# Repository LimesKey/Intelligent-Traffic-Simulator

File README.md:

# Intelligent-Traffic-Simulator

> [!NOTE]
> Work in progress - Everything has shown to be working individually but has not came together as a whole yet

Detect how hot wheels cars navigate streets and interact with stop lights and how this can be applied to the real world. Just a thing I made for class

It detects hot wheels cars via the three coils embedded in the PCB traces. The coils are hooked up to a 555 timer at around 200 KHz and when the hot wheels car is over the coil, the frequency changes which is detected by the ESP32 running a pulse counter script. Essentially a metal/object detector specifically calibrated for hot wheels cars.

Potentiometers are just for debugging / testing out various configurations. There is a multiplexer hooked up to the ESP32 so that one microcontroller can control multiple LEDs for multiple traffic lights.

I made some small mistakes, but I believe I updated the schematic to reflect the changes I made to make it work.

### Todo: 
* better ESD/current backflow protection 
* have esp32 fully inside PCB outline rather than sticking out
* remove extra testpoints / optvbvvcional components now that I know what works
* look into using a general oscillator rather than a 555 timer for better performance/cost
* somehow make the usb-c connector much easier to solder, it's killing me how difficult it is
* integrate `object-detection.ino` with `dutch_traffic_light_code.ino`

# Media
## JLCPCB Ordered, Hand Assembled

## KiCad
### PCB 3D Viewer
<div style="display:flex; justify-content:center; gap:16px;">

</div>

### Schematic

<h4 align="center">Main controller</h4>

<h4 align="center">555 Timer Circuitry</h4>

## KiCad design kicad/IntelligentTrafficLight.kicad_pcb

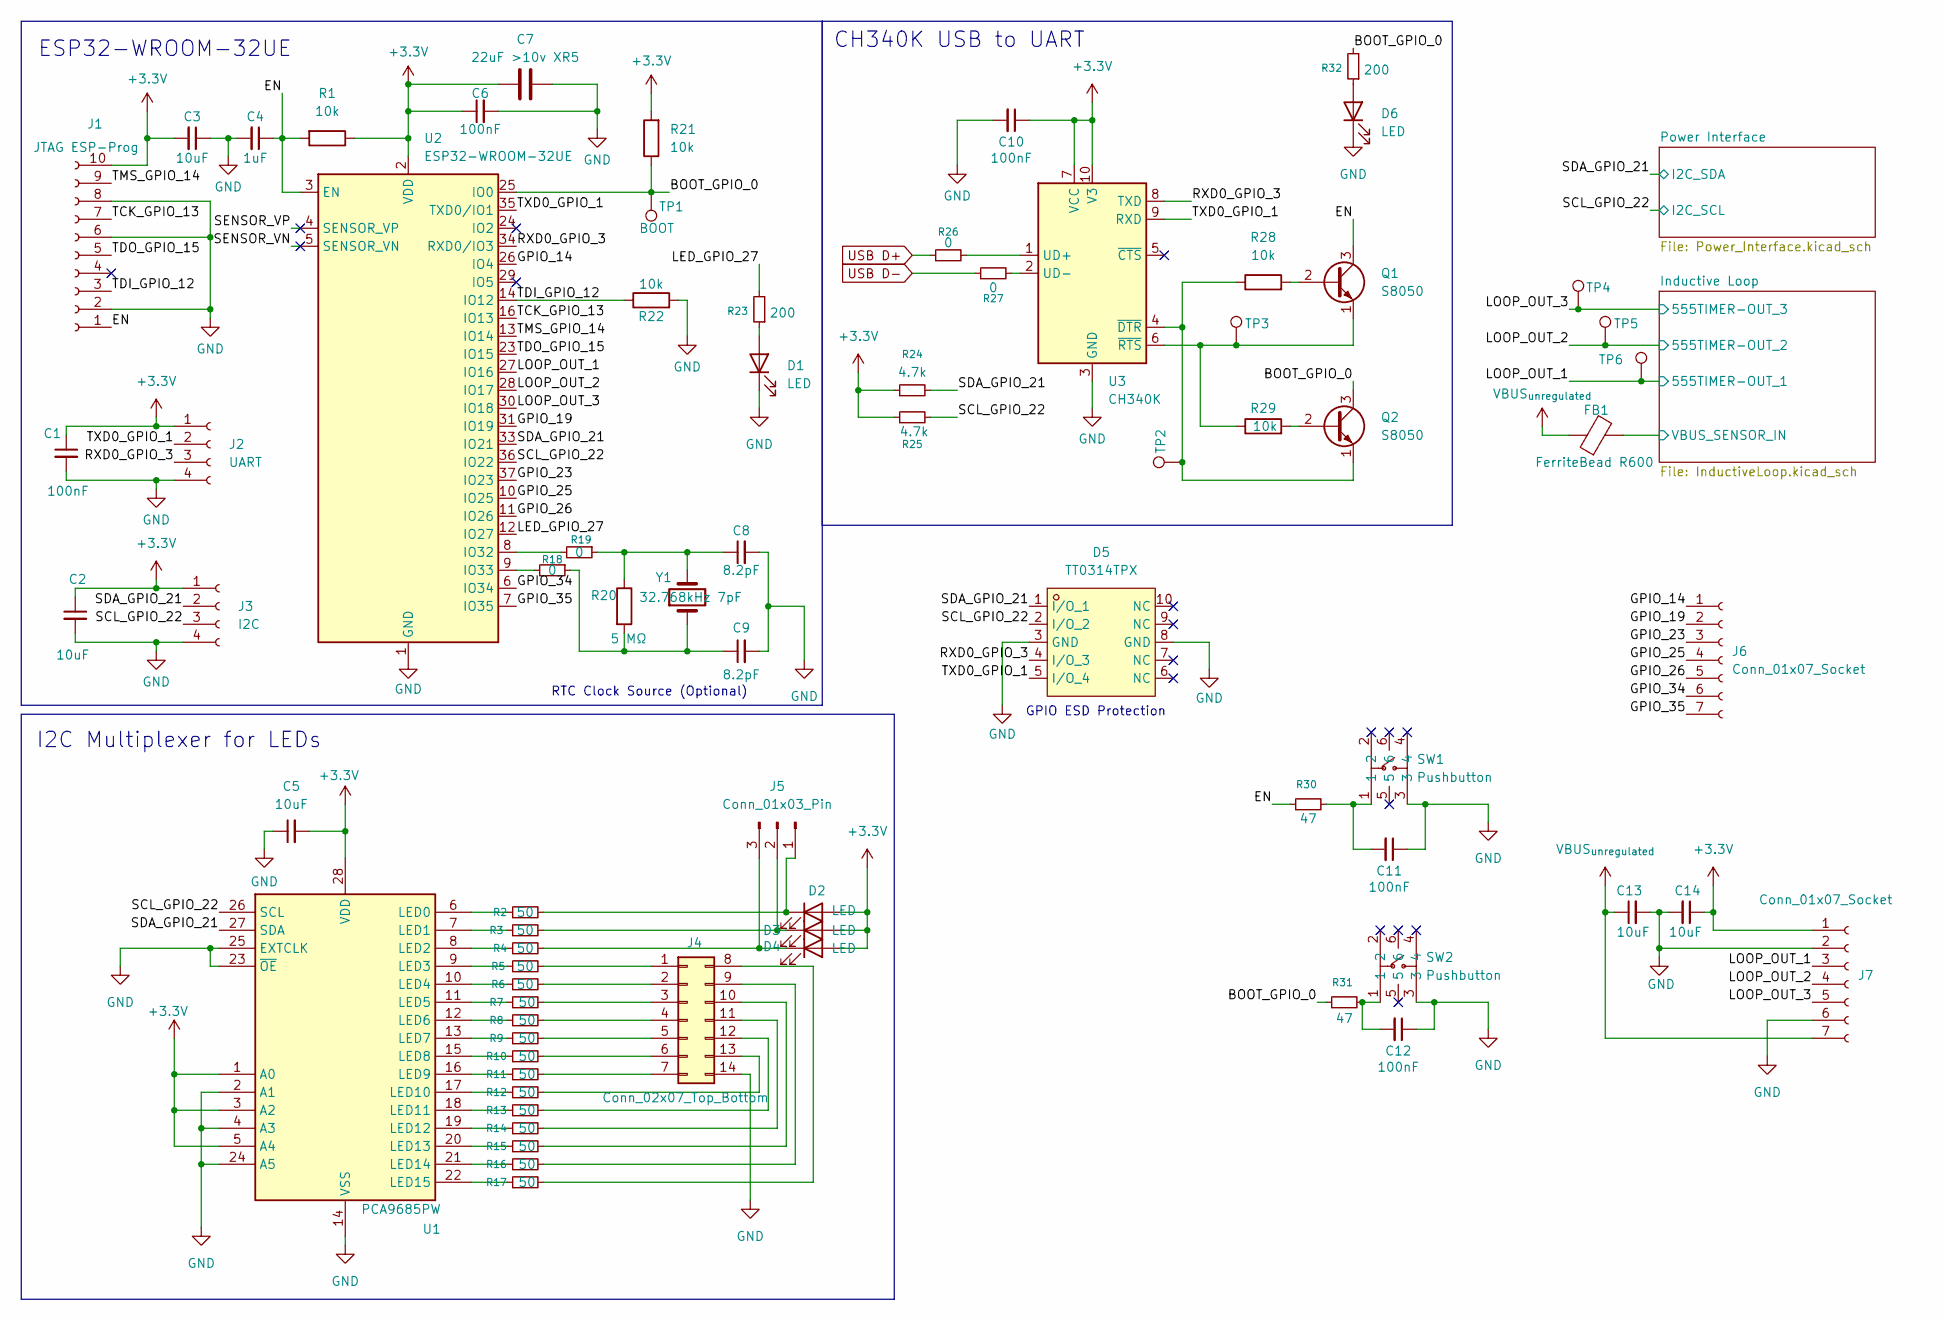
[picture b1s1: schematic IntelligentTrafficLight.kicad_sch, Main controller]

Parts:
C1, C6, C10, C11, C12: 100nF; C_0402_1005Metric
C2, C3, C5: 10uF; C_0402_1005Metric
C4: 1uF; C_0402_1005Metric
C7: 22uF >10v XR5; C_0805_2012Metric
C8, C9: 8.2pF; C_0402_1005Metric; LCSC Part C2857971
C13, C14: 10uF; C_0402_1005Metric; LCSC Part C33595851
D1, D2, D3, D4, D6: LED; LED_D5.0mm
D5: TT0314TPX; DFN2510-10_L2.5-W1.0-P0.50-BL; LCSC Part C5307962
FB1: FerriteBead R600; L_0603_1608Metric
J1: JTAG ESP-Prog; PinSocket_1x10_P2.54mm_Horizontal
J2: UART; PinSocket_1x04_P2.54mm_Horizontal
J3: I2C; PinSocket_1x04_P2.54mm_Horizontal
J4: Conn_02x07_Top_Bottom; PinSocket_2x07_P2.54mm_Horizontal
J5: Conn_01x03_Pin; PinHeader_1x03_P1.00mm_Vertical
J6, J7: Conn_01x07_Socket; PinSocket_1x07_P2.54mm_Horizontal
Q1, Q2: S8050; TO-92_Inline
R1, R21, R22, R28, R29: 10k; R_0402_1005Metric
R2, R3, R4, R5, R6, R7, R8, R9, R10, R11, R12, R13, R14, R15, R16, R17: 50; R_0402_1005Metric
R18, R19, R26, R27: 0; R_0603_1608Metric
R20: 5 MΩ; R_0402_1005Metric
R23, R32: 200; R_0402_1005Metric
R24, R25: 4.7k; R_0402_1005Metric
R30, R31: 47; R_0402_1005Metric
SW1, SW2: Pushbutton; SW-SMD_6P-L5.2-W5.2-P3.70-LS6.4; LCSC Part C2848968
TP1: BOOT; TestPoint_Bridge_Pitch2.54mm_Drill0.7mm
TP2: DTR; TestPoint_Bridge_Pitch2.54mm_Drill0.7mm
TP3: RTS; TestPoint_Bridge_Pitch2.54mm_Drill0.7mm
TP4: LOOP_OUT_3; TestPoint_Bridge_Pitch2.54mm_Drill0.7mm
TP5: LOOP_OUT_2; TestPoint_Bridge_Pitch2.54mm_Drill0.7mm
TP6: LOOP_OUT_1; TestPoint_Bridge_Pitch2.54mm_Drill0.7mm
U1: PCA9685PW; TSSOP-28_4.4x9.7mm_P0.65mm; LCSC Part C2678753
U2: ESP32-WROOM-32UE
U3: CH340K; SSOP-10-1EP_3.9x4.9mm_P1mm_EP2.1x3.3mm
Y1: 32.768kHz 7pF; Crystal_SMD_2012-2Pin_2.0x1.2mm_HandSoldering; LCSC Part C2905364

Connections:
+3.3V: C1.1, C2.1, C3.2, C5.2, C6.1, C7.1, C10.1, C14.1, D2.2 (A), D3.2 (A), D4.2 (A), J1.10, J2.1, J3.1, J7.1, R1.1, R21.2, R24.1, R25.1, U1.1 (A0), U1.3 (A2), U1.5 (A4), U1.28 (VDD), U2.2 (VDD), U3.7 (VCC), U3.10 (V3); also elsewhere on the board
/BOOT_GPIO_0: Q2.3 (C), R21.1, R31.1, R32.2, TP1.1 (1_1), U2.25 (IO0)
/EN: C4.1, J1.1, Q1.3 (C), R1.2, R30.1, U2.3 (EN)
/GPIO_14: J6.1, U2.26 (IO4)
/GPIO_19: J6.2, U2.31 (IO19)
/GPIO_23: J6.3, U2.37 (IO23)
/GPIO_25: J6.4, U2.10 (IO25)
/GPIO_26: J6.5, U2.11 (IO26)
/GPIO_34: J6.6, U2.6 (IO34)
/GPIO_35: J6.7, U2.7 (IO35)
/Inductive Loop/VBUS_SENSOR_IN: FB1.2; also elsewhere on the board
/LED_GPIO_27: R23.2, U2.12 (IO27)
/LOOP_OUT_1: J7.3, TP6.1 (1_1), U2.27 (IO16); also elsewhere on the board
/LOOP_OUT_2: J7.4, TP5.1 (1_1), U2.28 (IO17); also elsewhere on the board
/LOOP_OUT_3: J7.5, TP4.1 (1_1), U2.30 (IO18); also elsewhere on the board
/RXD0_GPIO_3: D5.4 (I/O_3), J2.3, U2.34 (RXD0/IO3), U3.8 (TXD)
/SCL_GPIO_22: D5.2 (I/O_2), J3.3, R25.2, U1.26 (SCL), U2.36 (IO22); also elsewhere on the board
/SDA_GPIO_21: D5.1 (I/O_1), J3.2, R24.2, U1.27 (SDA), U2.33 (IO21); also elsewhere on the board
/SENSOR_VN: U2.5 (SENSOR_VN)
/SENSOR_VP: U2.4 (SENSOR_VP)
/TCK_GPIO_13: J1.7, U2.16 (IO13)
/TDI_GPIO_12: J1.3, R22.1, U2.14 (IO12)
/TDO_GPIO_15: J1.5, U2.23 (IO15)
/TMS_GPIO_14: J1.9, U2.13 (IO14)
/TXD0_GPIO_1: D5.5 (I/O_4), J2.2, U2.35 (TXD0/IO1), U3.9 (RXD)
GND: C1.2, C2.2, C3.1, C4.2, C5.1, C6.2, C7.2, C8.2, C9.2, C10.2, C11.1, C12.1, C13.2, C14.2, D1.1 (K), D5.3 (GND), D5.8 (GND), D6.1 (K), J1.2, J1.6, J1.8, J2.4, J3.4, J4.14, J7.2, J7.6, R22.2, SW1.3, SW2.3, U1.2 (A1), U1.4 (A3), U1.14 (VSS), U1.23 (~OE), U1.24 (A5), U1.25 (EXTCLK), U2.1 (GND), U2.15 (GND), U2.38 (GND), U2.39 (GND), U3.3 (GND), U3.11 (GND); also elsewhere on the board
unnamed: C8.1, R19.1, R20.1, Y1.2
unnamed: C9.1, R18.1, R20.2, Y1.1
unnamed: C11.2, R30.2, SW1.1
unnamed: C12.2, R31.2, SW2.1
unnamed: D1.2 (A), R23.1
unnamed 35: D2.1 (K), J5.1, R2.2; also elsewhere on the board
unnamed: D3.1 (K), J5.2, R3.2
unnamed 37: D4.1 (K), J5.3, R4.2; also elsewhere on the board
unnamed: D6.2 (A), R32.1
unnamed 41: J4.1, R5.2; also elsewhere on the board
unnamed 42: J4.2, R6.2; also elsewhere on the board
unnamed: J4.3, R7.2
unnamed: J4.4, R8.2
unnamed: J4.5, R9.2
unnamed: J4.6, R10.2
unnamed: J4.7, R11.2
unnamed: J4.8, R17.2
unnamed: J4.9, R16.2
unnamed: J4.10, R15.2
unnamed: J4.11, R14.2
unnamed: J4.12, R13.2
unnamed: J4.13, R12.2
unnamed: Q1.2 (B), R28.2
unnamed: Q1.1 (E), R29.1, TP3.1 (1_1), U3.6 (~RTS)
unnamed: Q2.2 (B), R29.2
unnamed: Q2.1 (E), R28.1, TP2.1 (1_1), U3.4 (~DTR)
unnamed 75: R2.1, U1.6 (LED0); also elsewhere on the board
unnamed: R3.1, U1.7 (LED1)
unnamed 77: R4.1, U1.8 (LED2); also elsewhere on the board
unnamed 78: R5.1, U1.9 (LED3); also elsewhere on the board
unnamed 79: R6.1, U1.10 (LED4); also elsewhere on the board
unnamed: R7.1, U1.11 (LED5)
unnamed: R8.1, U1.12 (LED6)
unnamed: R9.1, U1.13 (LED7)
unnamed: R10.1, U1.15 (LED8)
unnamed: R11.1, U1.16 (LED9)
unnamed: R12.1, U1.17 (LED10)
unnamed: R13.1, U1.18 (LED11)
unnamed: R14.1, U1.19 (LED12)
unnamed: R15.1, U1.20 (LED13)
unnamed: R16.1, U1.21 (LED14)
unnamed: R17.1, U1.22 (LED15)
unnamed: R19.2, U2.8 (IO32)
unnamed: R18.2, U2.9 (IO33)
unnamed: R26.2, U3.1 (UD+)
unnamed: R27.2, U3.2 (UD-)
USB D+: R26.1; also elsewhere on the board
USB D-: R27.1; also elsewhere on the board
VBUS_{unregulated}: C13.1, FB1.1, J7.7; also elsewhere on the board

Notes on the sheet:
RTC Clock Source (Optional)
ESP32-WROOM-32UE
GPIO ESD Protection
I2C Multiplexer for LEDs
CH340K USB to UART

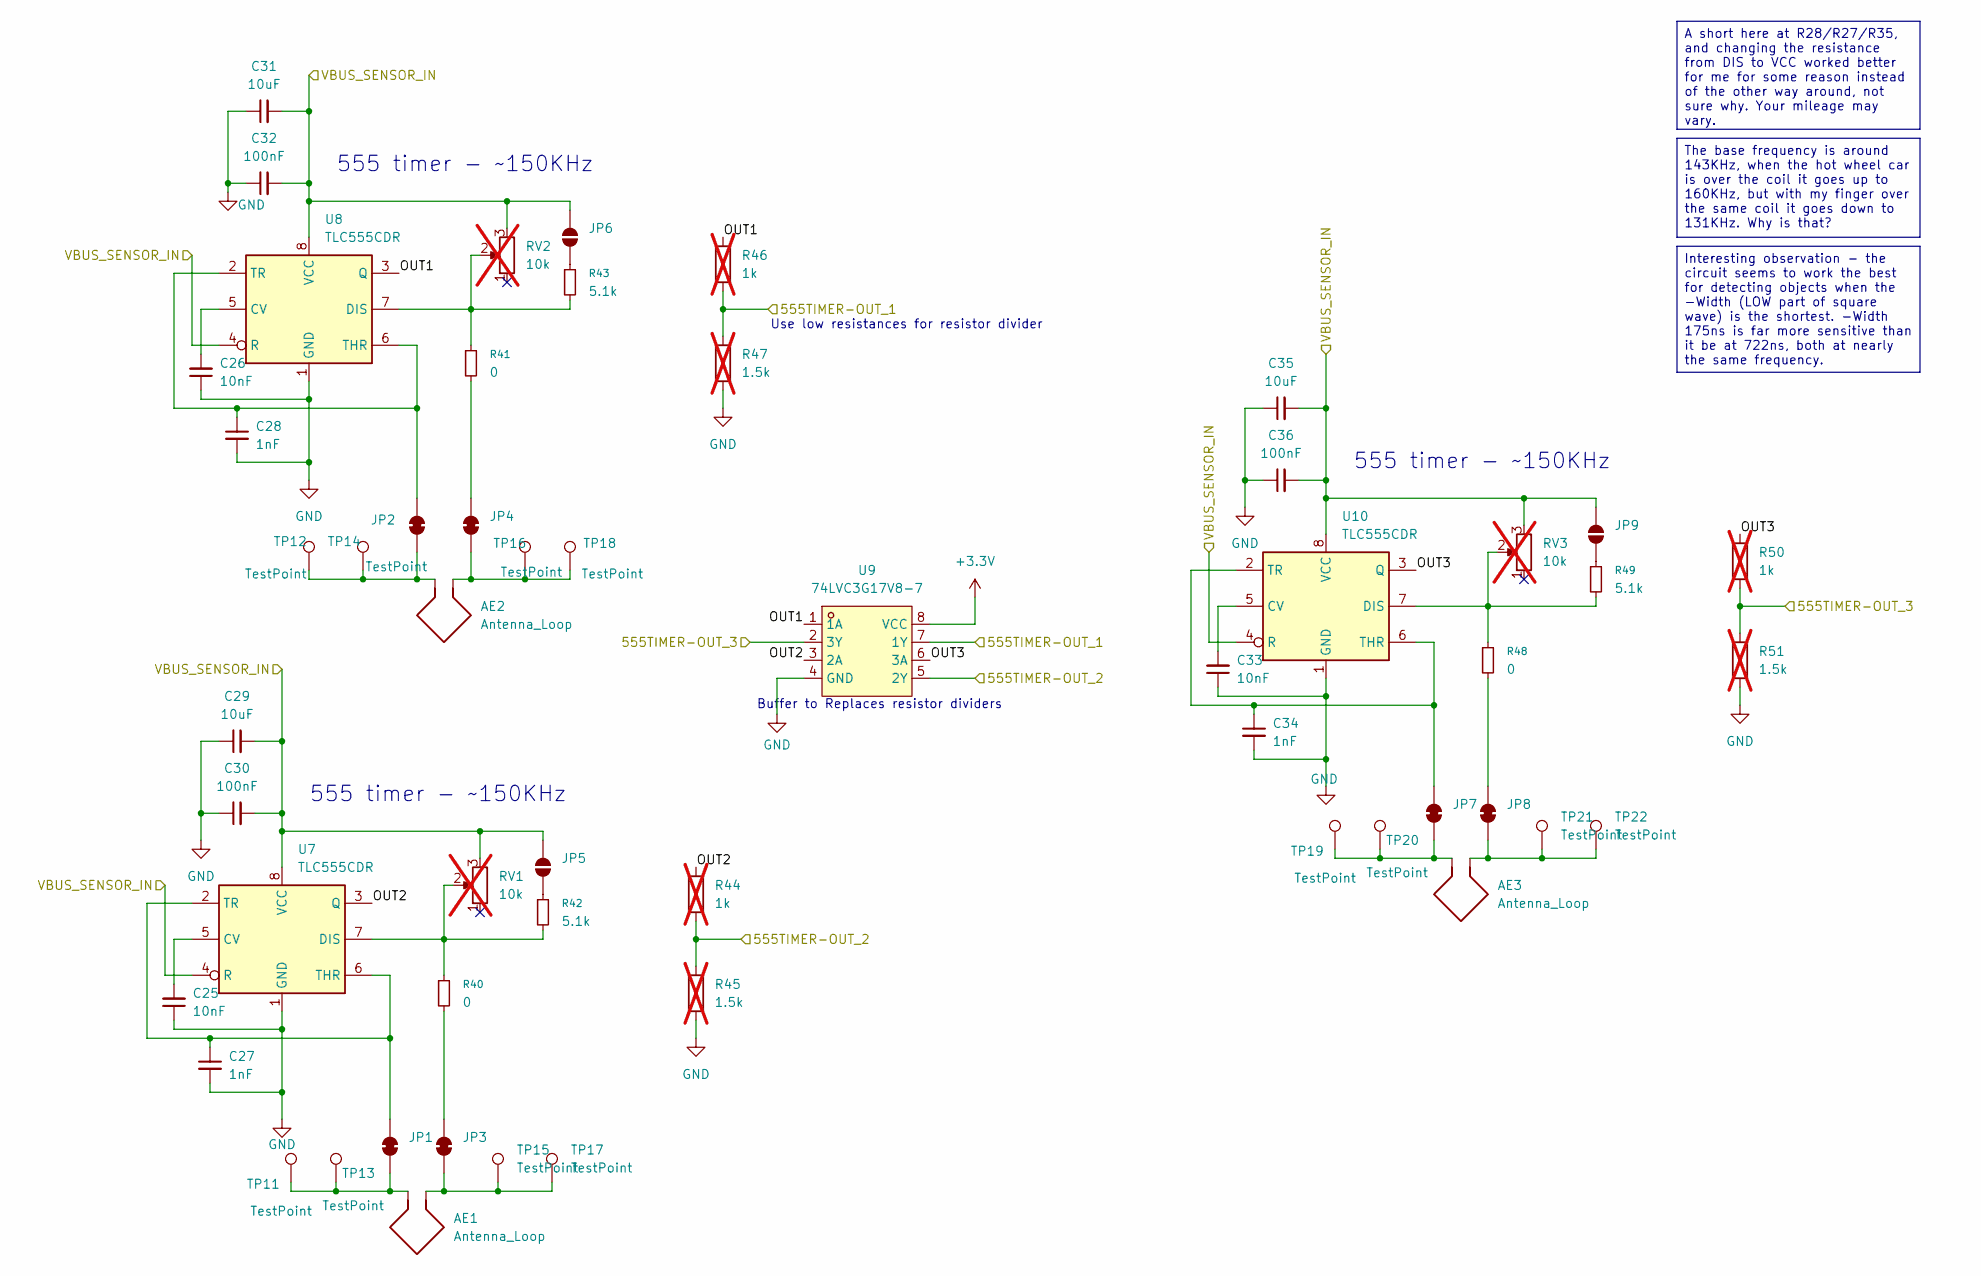
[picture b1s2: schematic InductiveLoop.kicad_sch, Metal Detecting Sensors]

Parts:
AE1, AE2, AE3: Antenna_Loop; HOTWHEEL_DETECTOR
C25, C26, C33: 10nF; C_0402_1005Metric
C27, C28, C34: 1nF; C_0402_1005Metric
C29, C31, C35: 10uF; C_0402_1005Metric
C30, C32, C36: 100nF; C_0402_1005Metric
JP1, JP2, JP3, JP4, JP7, JP8: SolderJumper_2_Bridged; SolderJumper-2_P1.3mm_Bridged_RoundedPad1.0x1.5mm
JP5, JP6, JP9: SolderJumper_2_Open; SolderJumper-2_P1.3mm_Open_RoundedPad1.0x1.5mm
R40, R41, R48: 0; R_0402_1005Metric
R42, R49: 5.1k; R_0402_1005Metric
R43: 5.1k; R_Axial_DIN0207_L6.3mm_D2.5mm_P10.16mm_Horizontal
R44, R46, R50: 1k; R_0402_1005Metric; not fitted
R45, R47, R51: 1.5k; R_0402_1005Metric; not fitted
RV1, RV2, RV3: 10k; Potentiometer_Bourns_3386P_Vertical; LCSC Part C118956; not fitted
TP11, TP12, TP13, TP14, TP15, TP16, TP17, TP18, TP19, TP20, TP21, TP22: TestPoint; PinSocket_1x01_P2.54mm_Vertical
U7, U8, U10: TLC555CDR; SOIC-8_3.9x4.9mm_P1.27mm; LCSC Part C6986
U9: 74LVC3G17V8-7; VSSOP-8_L2.1-W2.4-P0.50-LS3.2-BL; MPN 74LVC3G17V8-7; LCSC Part C19948350

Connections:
+3.3V: U9.8 (VCC); also elsewhere on the board
/Inductive Loop/OUT1: R46.1, U8.3 (Q), U9.1 (1A)
/Inductive Loop/OUT2: R44.1, U7.3 (Q), U9.3 (2A)
/Inductive Loop/OUT3: R50.1, U9.6 (3A), U10.3 (Q)
/Inductive Loop/VBUS_SENSOR_IN: C29.2, C30.2, C31.2, C32.2, C35.2, C36.2, JP5.2 (B), JP6.2 (B), JP9.2 (B), RV1.3, RV2.3, RV3.3, U7.4 (R), U7.8 (VCC), U8.4 (R), U8.8 (VCC), U10.4 (R), U10.8 (VCC); also elsewhere on the board
/LOOP_OUT_1: R46.2, R47.1, U9.7 (1Y); also elsewhere on the board
/LOOP_OUT_2: R44.2, R45.1, U9.5 (2Y); also elsewhere on the board
/LOOP_OUT_3: R50.2, R51.1, U9.2 (3Y); also elsewhere on the board
GND: C25.1, C26.1, C27.2, C28.2, C29.1, C30.1, C31.1, C32.1, C33.1, C34.2, C35.1, C36.1, R45.2, R47.2, R51.2, U7.1 (GND), U8.1 (GND), U9.4 (GND), U10.1 (GND); also elsewhere on the board
unnamed: AE1.2, JP1.1 (A), TP11.1 (1_1), TP13.1 (1_1)
unnamed: C27.1, JP1.2 (B), U7.2 (TR), U7.6 (THR)
unnamed: AE2.2, JP2.1 (A), TP12.1 (1_1), TP14.1 (1_1)
unnamed: C28.1, JP2.2 (B), U8.2 (TR), U8.6 (THR)
unnamed: AE1.1, JP3.1 (A), TP15.1 (1_1), TP17.1 (1_1)
unnamed: JP3.2 (B), R40.2
unnamed: AE2.1, JP4.1 (A), TP16.1 (1_1), TP18.1 (1_1)
unnamed: JP4.2 (B), R41.2
unnamed: JP5.1 (A), R42.1
unnamed: JP6.1 (A), R43.1
unnamed: AE3.2, JP7.1 (A), TP19.1 (1_1), TP20.1 (1_1)
unnamed: C34.1, JP7.2 (B), U10.2 (TR), U10.6 (THR)
unnamed: AE3.1, JP8.1 (A), TP21.1 (1_1), TP22.1 (1_1)
unnamed: JP8.2 (B), R48.2
unnamed: JP9.1 (A), R49.1
unnamed: C25.2, U7.5 (CV)
unnamed: R40.1, R42.2, RV1.2, U7.7 (DIS)
unnamed: C26.2, U8.5 (CV)
unnamed: R41.1, R43.2, RV2.2, U8.7 (DIS)
unnamed: C33.2, U10.5 (CV)
unnamed: R48.1, R49.2, RV3.2, U10.7 (DIS)

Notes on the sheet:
Buffer to Replaces resistor dividers
555 timer - ~150KHz
Use low resistances for resistor divider
Interesting observation - the circuit seems to work the best for detecting objects when the -Width (LOW part of square wave) is the shortest. -Width 175ns is far more sensitive than it be at 722ns, both at nearly the same frequency.
The base frequency is around 143KHz, when the hot wheel car is over the coil it goes up to 160KHz, but with my finger over the same coil it goes down to 131KHz. Why is that?
A short here at R28/R27/R35, and changing the resistance from DIS to VCC worked better for me for some reason instead of the other way around, not sure why. Your mileage may vary.

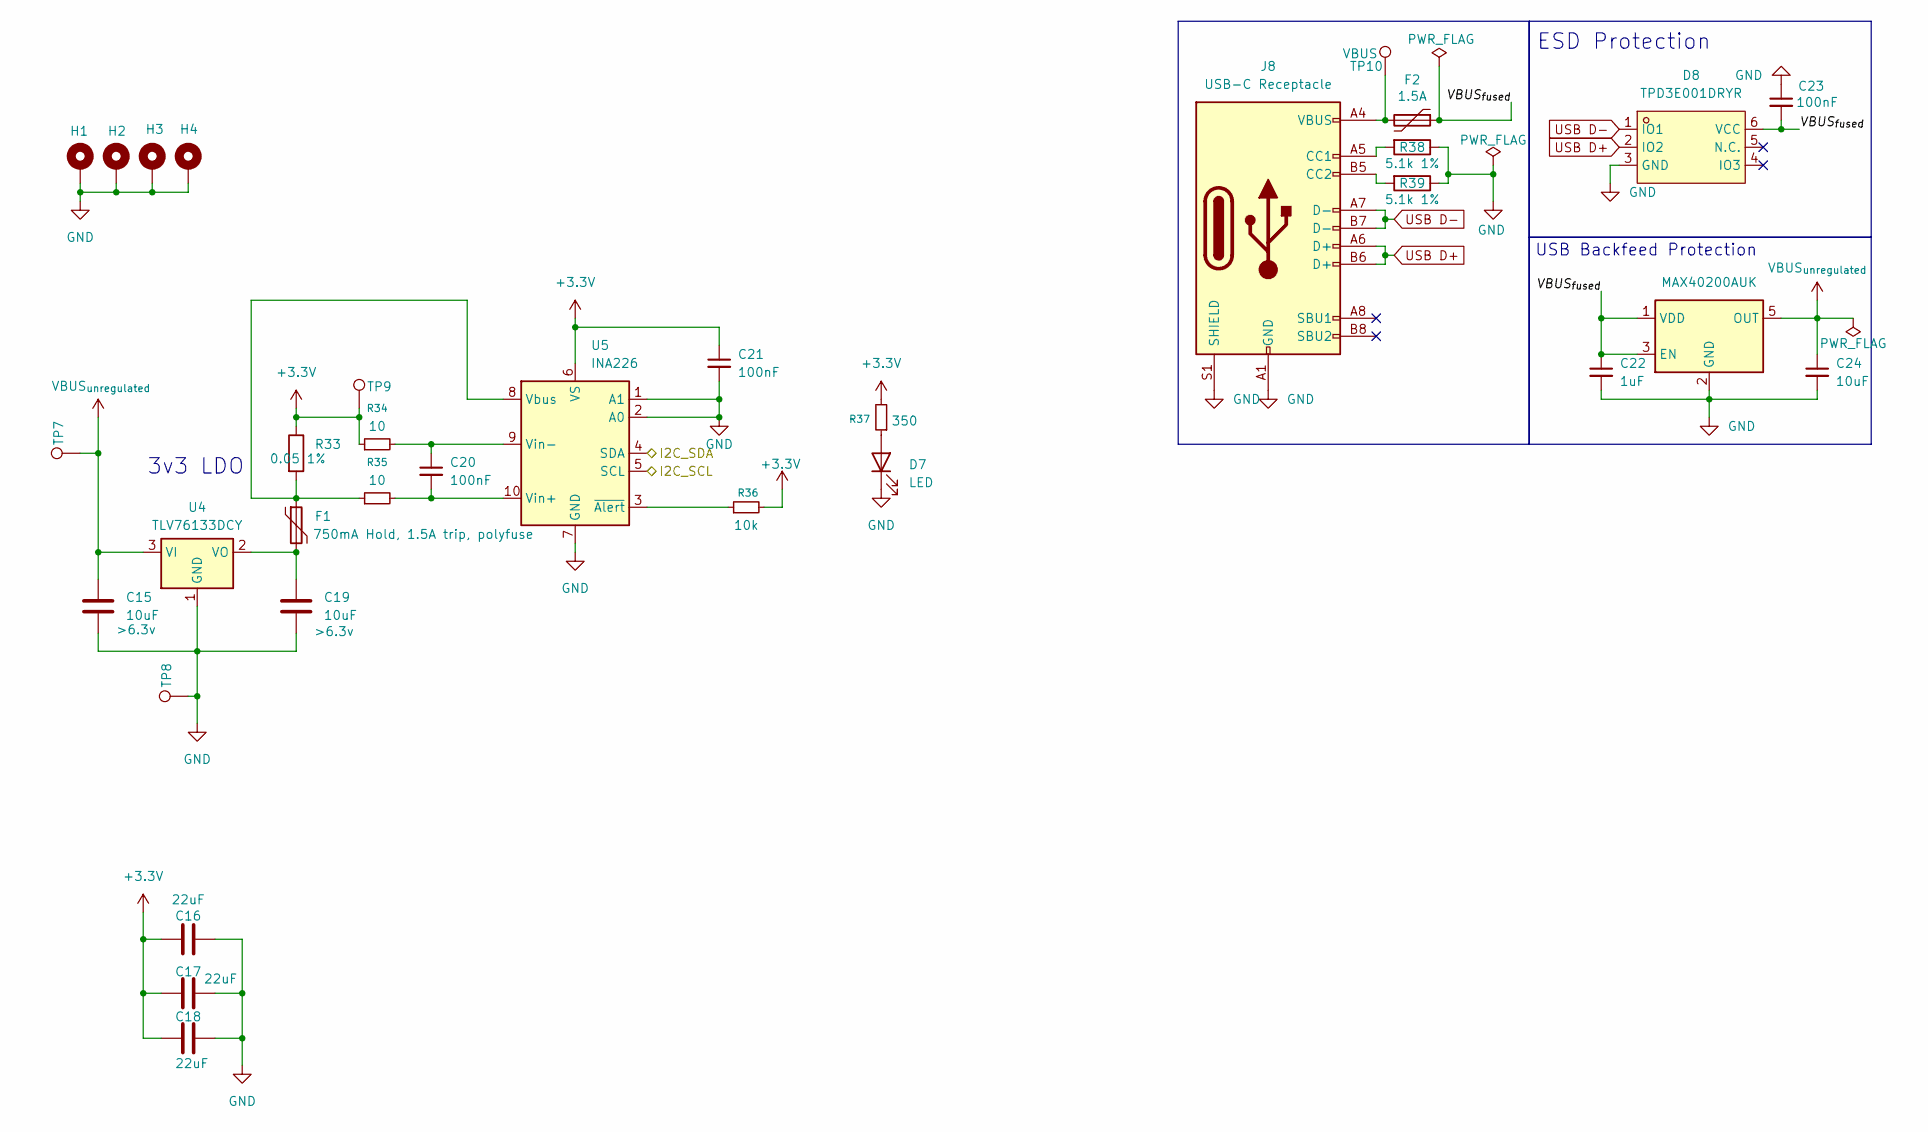
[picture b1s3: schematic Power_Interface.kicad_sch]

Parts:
C15, C19: 10uF; C_0402_1005Metric; Voltage Rating >6.3v
C16, C17, C18: 22uF; C_0805_2012Metric; LCSC Part C7472967
C20, C21: 100nF; C_0402_1005Metric
C22: 1uF; C_0402_1005Metric
C23: 100nF; C_0402_1005Metric; LCSC Part C392963
C24: 10uF; C_0402_1005Metric
D7: LED; LED_D5.0mm
D8: TPD3E001DRYR; Texas_USON-6_1x1.45mm_P0.5mm_SMD; LCSC Part C5122047
F1: 750mA Hold, 1.5A trip, polyfuse; Fuse_1812_4532Metric; LCSC Part C49318440
F2: 1.5A; Fuse_1206_3216Metric_Pad1.42x1.75mm_HandSolder; LCSC Part C883133
H1, H2, H3, H4: MountingHole_Pad; MountingHole_3.2mm_M3_Pad
J8: USB-C Receptacle; USB_C_Receptacle_G-Switch_GT-USB-7010ASV; LCSC Part C963413
R33: 0.05 1%; R_2512_6332Metric; LCSC Part C49164908
R34, R35: 10; R_0402_1005Metric
R36: 10k; R_0402_1005Metric
R37: 350; R_0402_1005Metric
R38, R39: 5.1k 1%; R_0402_1005Metric; LCSC Part C2906874
TP7: VBUSunreg; TestPoint_Bridge_Pitch2.54mm_Drill0.7mm
TP8: LOOP_OUT_2; TestPoint_Bridge_Pitch2.54mm_Drill0.7mm
TP9: 3V3; TestPoint_Bridge_Pitch2.54mm_Drill0.7mm
TP10: VBUS; PinSocket_1x01_P2.54mm_Vertical
U4: TLV76133DCY; SOT-223-3_TabPin2; LCSC Part C7527500
U5: INA226; TSSOP-10_3x3mm_P0.5mm
U6: MAX40200AUK; SOT-23-5

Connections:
+3.3V: C16.1, C17.1, C18.1, C21.1, R33.1, R34.1, R36.2, R37.2, TP9.1 (1_1), U5.6 (VS); also elsewhere on the board
/Power Interface/VBUS_{fused}: C22.1, C23.2, D8.6 (VCC), F2.1, U6.1 (VDD), U6.3 (EN)
/SCL_GPIO_22: U5.5 (SCL); also elsewhere on the board
/SDA_GPIO_21: U5.4 (SDA); also elsewhere on the board
GND: C15.2, C16.2, C17.2, C18.2, C19.2, C21.2, C22.2, C23.1, C24.2, D7.1 (K), D8.3 (GND), H1.1 (1_1), H2.1 (1_1), H3.1 (1_1), H4.1 (1_1), J8.A1 (GND), J8.A12 (GND), J8.B1 (GND), J8.B12 (GND), J8.S1 (SHIELD), R38.1, R39.1, TP8.1 (1_1), U4.1 (GND), U5.1 (A1), U5.2 (A0), U5.7 (GND), U6.2 (GND); also elsewhere on the board
unnamed: D7.2 (A), R37.1
unnamed: F2.2, J8.A4 (VBUS), J8.A9 (VBUS), J8.B4 (VBUS), J8.B9 (VBUS), TP10.1 (1_1)
unnamed: J8.A5 (CC1), R38.2
unnamed: J8.B5 (CC2), R39.2
unnamed: C19.1, F1.2, U4.2 (VO)
unnamed: F1.1, R33.2, R35.1, U5.8 (Vbus)
unnamed: C20.2, R35.2, U5.10 (Vin+)
unnamed: C20.1, R34.2, U5.9 (Vin-)
unnamed: R36.1, U5.3 (~Alert)
USB D+: D8.2 (IO2), J8.A6 (D+), J8.B6 (D+); also elsewhere on the board
USB D-: D8.1 (IO1), J8.A7 (D-), J8.B7 (D-); also elsewhere on the board
VBUS_{unregulated}: C15.1, C24.1, TP7.1 (1_1), U4.3 (VI), U6.5 (OUT); also elsewhere on the board

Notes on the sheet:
3v3 LDO
USB Backfeed Protection
ESD Protection

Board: 4 copper layers, 168 parts (71 on the bottom side), 107 nets, no tracks yet.

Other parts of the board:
R2#2, R4#2, R5#2, R6#2: 50; R_0402_1005Metric
kibuzzard-691D01BA: G***; kibuzzard-691D01BA
kibuzzard-691D028C: G***; kibuzzard-691D028C

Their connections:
unnamed 35: R2#2.2; also elsewhere on the board
unnamed 37: R4#2.2; also elsewhere on the board
unnamed 41: R5#2.2; also elsewhere on the board
unnamed 42: R6#2.2; also elsewhere on the board
unnamed 75: R2#2.1; also elsewhere on the board
unnamed 77: R4#2.1; also elsewhere on the board
unnamed 78: R5#2.1; also elsewhere on the board
unnamed 79: R6#2.1; also elsewhere on the board

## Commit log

2025-12-21 add code & website & pcb files
2025-12-21 touchup readme
2025-12-21 fix css so images are side by side
2025-12-21 fix 2
2025-12-21 touchup filenames & directories, remove some files
2025-12-21 website styling changes
2025-12-21 ehh idk
2025-12-22 add comments to kicad schematic
2026-03-30 small pcb change
2026-05-07 update!
2026-05-09 more updates
2026-05-11 nothing
